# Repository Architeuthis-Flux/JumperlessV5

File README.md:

###### The next generation [jumperless](https://github.com/Architeuthis-Flux/Jumperless) breadboard
---
## If you got here by scanning the QR code on your box and want to know how to use this thing, the [There's a readthedocs.io site here](https://jumperless-docs.readthedocs.io/en/latest).
#### Don't hesitate to ask me *anything* in [Discord](https://discord.gg/Zvv7Dvgxa5) or wherever. Seriously, even if you think it's a dumb question, someone else probably has it too, so it helps me out a lot to know what to put in the guide.

Watch the launch video here:

  ---

# What is it?

Jumperless V5 lets you prototype like a nerdy wizard who can see electricity and conjure jumpers with a magic wand. It’s an Integrated Development Environment (IDE) for hardware, with an analog-by-nature RP2350B dev board, a drawer full of wires, and a workbench full of test equipment (including a power supply, a multimeter, an oscilloscope, a function generator, and a logic analyzer) all crammed inside a breadboard.

You can connect any point to any other using software-defined jumpers, so the four individually programmable ±8 V power supplies; ten GPIO; and seven management channels for voltage, current, and resistance can all be connected anywhere on the breadboard or the Arduino Nano header. RGB LEDs under each hole turn the breadboard itself into a display that provides real-time information about whatever’s happening in your circuit.

It's not just about being too lazy to plug in some jumpers. With software controlled wiring, the circuit *itself* is now [***scriptable***](08-micropython.md), which opens up a world of infinite crazy new things you could never do on a regular breadboard. Have a script try out every combination of parts until it does what you want (*à la* [evolvable hardware](https://evolvablehardware.org/)), automatically switch around audio effects on the fly, characterize some unknown chip with the part numbers sanded off, or don't bother with any of that and just [play Doom on it](https://www.youtube.com/watch?v=xWYWruUO0F4).

But more likely, you'll be using it to get circuits from your brain into hardware with so little friction it feels like you're just thinking them into existence. So yeah, wizard shit.

### **These are the docs where you will learn how to wield your new powers**

If you don't already have one,
## [Get a Jumperless V5 on Crowd Supply](https://www.crowdsupply.com/architeuthis-flux/jumperless-v5)

## Getting Started

## Documentation Sections

- **[Basic Controls](https://jumperless-docs.readthedocs.io/en/latest/01-basic-controls/)** - Learn how to use the probe, click wheel, and slot system
- **[The App](https://jumperless-docs.readthedocs.io/en/latest/03-app/)** - For talking to your Jumperless, importing from Wokwi, and flashing Arduino sketches
- **[OLED](https://jumperless-docs.readthedocs.io/en/latest/04-oled/)** - Add a better display
- **[Arduino](https://jumperless-docs.readthedocs.io/en/latest/05-arduino/)** - UART passthrough and automatic flashing
- **[Configuration](https://jumperless-docs.readthedocs.io/en/latest/06-config)** - Persistent settings
- **[Debugging](https://jumperless-docs.readthedocs.io/en/latest/07-debugging)** - Crossbar, bridge, and net list views
- **[File Manager](https://jumperless-docs.readthedocs.io/en/latest/08-file-manager)** - Filesystem access, YAML slot file editing, and text editor
- **[MicroPython](https://jumperless-docs.readthedocs.io/en/latest/08-micropython)** - Use the onboard MicroPython interpreter
- **[Odds and Ends](https://jumperless-docs.readthedocs.io/en/latest/09-odds-and-ends)** - Stuff I couldn't think of a good category for
- **[3D Printable Stand](https://jumperless-docs.readthedocs.io/en/latest/10-3d-stand)** - Print your own stand
- **[Writing Native Apps](https://jumperless-docs.readthedocs.io/en/latest/11-WritingApps)** - Dig into the actual firmware and write your own apps
- **[Glossary](https://jumperless-docs.readthedocs.io/en/latest/99-glossary)** - Key terms including slots, nodes, bridges, and the W command

---

## Find Me On The Internet

Join the [Discord](https://discord.gg/bvacV7r3FP) for pretty much instant answers to your questions

<div class="social-icons">

</div>

---

The 4 individually programmable ±8V power supplies, 5 voltage/current/resistance measurement channels, and 10 GPIO can all be connected anywhere on the breadboard or the Arduino Nano header. Connections made with its matrix of 12 analog crossbar switches can be changed in just a few microseconds, so measurements and GPIO can multiplexed to cover the entire board at once.

V5 is a major redesign of the original [Jumperless](https://github.com/Architeuthis-Flux/Jumperless). Having a few hundred people out there using Jumperlesses, sharing ideas, and [writing their](https://github.com/nilclass/jlctl) [own apps](https://github.com/nilclass/jumperlab) gave me a long enough list of things I wish I had done that I felt it was time to push the design even further. Now that the fundamentals are battle-tested (switching matrix, power supply, routing algorithm), Jumperless V5 can add some even crazier new stuff like; an ungodly number (445) of LEDs, a built in rotary encoder/switch, daisy chain headers, individually programmable power rails, and an isolated, always-on probing system. 

These additions may seem somewhat minor, but they fundamentally change the way using a Jumperless V5 *feels*. It's intuitive enough that it quickly just becomes "part of your brain" in the same way your computer does. And it's easy to forget this isn't how prototyping stuff on a breadboard always has been.

https://github.com/user-attachments/assets/c78493ee-f2cd-4704-bab7-26346f978c54

https://github.com/user-attachments/assets/168cb387-934b-4a25-b30d-b696312ee0e1

# For People Who Like Reading (btw all of this is a bit dated and some details have changed since then)
You're flipping through a comic book and see an ad in the back for some X-ray glasses. You put some coins in an envelope and send it off (because it's like 50 years ago in this made up scenario) and get back some spectacles. You immediately look up at the night sky towards the galactic center for Sagittarius A* and don't see a thing; you've been had. You go back to prototyping your new Eurorack module (because that's what I assume everyone was doing in the early 80's) and forget to take them off. 

You notice that you can now see electrons flowing, capacitors charging, frequencies changing, UART messages passing, all right there on your breadboard. Those aren't X-ray specs, they're electron specs, even better.  

###### //When the prototypes get here on Monday, I'll take proper photos and these will be replaced

*Jumperless V5 is that pair of X-ray spectacles.* Like all the fancy test equipment covering our workbenches, it converts the things that our hunter-gatherer-ass MK 1 eyeballs can't perceive into something they can. The difference is that it does it for everything, everywhere, exactly where it's happening with an RGB LED under every hole. 

Now you're prototyping in God Mode, never again will you spend 2 hours testing every possible issue just to find that your Tx and Rx lines are swapped, or you forgot to hook up the Vcc pin, or some other thing that seems absolutely obvious in retrospect but you simply didn't have the information until you went down the list and checked each thing that could possibly go wrong.

Jumper wires are another time-consuming, flow-breaking thing, so let's get rid of those too. To be able to read and write anything everywhere, it also needs to be fully jumperless, so any rows on the breadboard (and the Arduino Nano header) can be connected to any other, as well as any of the 4 programmable power supplies, 3 analog measurement channels, 2 current/resistance sensors, (supplies and measurement are all good to +-8V), or 10 GPIO (4 are 5V logic, 6 are 3.3V. All 10 can instead be routed to another daisy-chained Jumperless as fully analog connections.) 

This isn't meant to abstract away the tactile process of prototyping under a layer of software. In fact, it's just the opposite, not having your circuit hidden under a tangled mass of jumper wires gives you a breadboard that is understandable at a glance and almost reads like a schematic. You can just drop a measurement anywhere and have it displayed on the LEDs under that row so you will immediately see if anything changes in real time, so you can get a much more intuitive sense about *why* things work (or don't). It's about cutting down on the debugging bullshit and letting the grander plans for what you're building flow freely. Ideas happen at their own pace, and getting stuck on the finicky details of circuit design can break the creative momentum. 

The probe, rotary encoder, and onboard menus make connecting to a computer optional. You can do everything with only USB C power. Your past projects are saved into onboard flash as simple text files that can be uploaded to your computer and shared.

Breadboards should be a playground, and now you can attach a debug probe to them.

https://github.com/Architeuthis-Flux/JumperlessV5/assets/20519442/a3d5ecf4-4665-409d-bab6-2a62fbbe0eb7

Now you have a breadboard with:

- 4 x 12 bit DACs ([MCP4278](https://www.microchip.com/en-us/product/mcp4728)) buffered and shifted to ±8V through high current op amps ([2 L272D](https://estore.st.com/en/l272d-cpn.html))
- 3 x 12 bit ADCs (built into the RP2040) double buffered and level shifted (2 LM324) to read ±8V 
- 2 x 12 bit current/voltage sensors ([INA219](https://www.ti.com/product/INA219)) which can also be used to measure resistance
- 4 x 5V logic level GPIO ([MCP23S17](https://www.microchip.com/en-us/product/mcp23s17))
- 6 x 3.3V logic level GPIO ([RP2040](https://www.raspberrypi.com/documentation/microcontrollers/rp2040.html)) which can also be hardware I2C, UART, or SPI
- 1 x ±8V op amp noninverting buffer ([LM324](https://www.ti.com/product/LM324B))
- 2 x 14 pin daisy chain headers on either side to pass 8 analog signals + SPI + Power to another Jumperless
- A probe to select rows without affecting connections (TRRRS jack with I2C)
- A rotary encoder / switch ([SIQ-02FVS3](https://www.lcsc.com/product-detail/Rotary-Encoders_Mitsumi-Electric-SIQ-02FVS3_C2925423.html))
- 445 addressable RGB LEDs ([XL-1010RGBC](https://www.lcsc.com/product-detail/Light-Emitting-Diodes-LED_XINGLIGHT-XL-1010RGBC-WS2812B_C5349953.html))

You can see how all this stuff is connected in the [schematic](https://kicanvas.org/?github=https://github.com/Architeuthis-Flux/JumperlessV5/blob/main/Hardware/JumperlessV5hw/JumperlessV5hw.kicad_sch).

Or check out the [PCB](https://kicanvas.org/?github=https://github.com/Architeuthis-Flux/JumperlessV5/blob/main/Hardware/JumperlessV5hw/JumperlessV5hw.kicad_pcb) and [GitHub repo](https://github.com/Architeuthis-Flux/JumperlessV5)

All these things are routable to anywhere on the breadboard or Nano header in a few microseconds under the control of the onboard RP2040. This freedom to script connections and measurements and route outputs anywhere presumably makes just about any random circuit on the Jumperless V5 Turing complete. There are an infinite number of things you could make this thing do, and the Prime Directive is to make those awesome hacks as simple and straightforward to pull off as possible. 

But for now, I'll only talk about things I've written firmware for that is currently supported without any hacking required.

Jumperless V5 accepts commands and stores connections in a ridiculously simple, human readable format that you can just drop onto the board as a text file. You can save a bunch of these net lists into persistent storage and switch between them at your whim. It will even accept connections from whatever's plugged into the Nano header (or anywhere else on the board over UART).

```
f {ADC1-10, 15-48, TOP_RAIL-17, TOP_RAIL>6.5V, D0-UART_Rx, D1-UART_Tx, }
```
⬆︎ *that's it, that's everything you need to send it to make things happen*

You can see how all that firmware works in the [firmware section of the GitHub repo]([https://github.com/Architeuthis-Flux/JumperlessV5](https://github.com/Architeuthis-Flux/JumperlessV5/tree/main/JumperlessV5firmware))

## The Probe
Jumperless V5 uses a string of 92 ±0.1% precision resistors in a huge voltage divider and one of the ADC channels to sense which number the probe is poking. The probe itself is very simple, just a button, an LED, and a pokey needle to touch the sensing pads. It connects to the main board with a TRRRS 1/8" audio jack. It also has I2C and power available on there for future hacking purposes (in case someone wants to stick an OLED on the probe, the code already does send signals for an SSD1306 display). 

If you happen to misplace your probe, the way it's designed allows you to just plug in any random 1/8" audio cable and poke out connections with the tip.

###### Just pretend this has an audio cable stuck to the back and it's sitting on a V5

## The App
The desktop app allows you to assign up to 8 [Wokwi](https://wokwi.com/) projects to separate slots that are polled for changes and automatically updated on the Jumperless V5 (within half a second of clicking Save). Or if you don't want to use Wokwi, it simply acts as a regular terminal emulator like PuTTY, xTerm, Serial, etc. You could also just use any of those, the menus are sent and handled on the Jumperless itself, the Jumperless desktop app just adds automatic firmware updates, Wokwi polling, and arduino-cli for flashing code from your Wokwi sketch to the Arduino via a single USB cable.

## Serial/I2C/SPI/MIDI
Jumperless V5 can sniff or write any UART, I2C, SPI, or MIDI signals on the board. It can be set to either print whatever it reads on the breadboard LEDs, turning the Jumperless into a serial monitor and/or show up as 2 USB devices to your computer and give you bidirectional communication through that other port. 
Look at that, Jumperless just saved you $3 on one of those little USB-UART boards, it practically pays for itself!!1!

## Slots/Music
The firmware saves multiple netlists in separate text files. You can save/load/manage the various slots through a serial terminal, the onboard menus, or even crazier things like having the slot change based on a Eurorack CV (control voltage) signal or whatever. So Jumperless can be incorporated into your modular synth setup as a way to switch between a bunch of patches live on the fly. The switchover time from one setup to another is quick enough to be inaudible.

## Voltage/Current Limits
The CMOS analog switches inside these CH446Qs can only block or pass voltages that are between their power supply rails. They're powered with an [LT1054CP](https://www.ti.com/product/LT1054) charge pump voltage doubler/inverter circuit that produces ~±9V. So it can handle any voltages between +9V and -9V and ~100mA per connection.
You may notice that these values are well outside the absolute maximum ratings (14.6V and 10mA per connection) listed in the CH446Q datasheet. That's because they are, all the specifications of the CH446Q get better as the supply voltage increases, so I'm exploiting the arcane weirdness of CMOS to get closer to an ideal switch. All of this is unchanged from the original Jumperless, so it's been well tested. 

## On resistance
Okay, here's the main bummer here. As it turns out, we live in a universe governed by both physics and capitalism, so manufacturers only make chips they think people will buy. The [CH446Q](https://www.wch-ic.com/products/CH446.html) (and the [MT8816](https://www.microsemi.com/product-directory/analog-cross-point-switches/4920-mt8816) it was based on) were made with radio, video, and audio in mind, which is much more concerned with frequency response than acting like an idealized jumper wire that can pass a bunch of current. So the total resistance for a jumperless connection is ~90Ω (45Ω for each pass through an overdriven crosspoint switch). For most circuits, this really doesn't have a noticeable effect. The beauty of the Jumperless V5 is that it can show you when that resistance is affecting your circuit and tell you to place an old-school jumper wire on that connection like it's the 1800s.

###### If this campaign does well enough, the next project will be making a general purpose crossbar switch out of beefy MOSFETs and [floating gate](https://en.wikipedia.org/wiki/Floating-gate_MOSFET) drivers to get the voltage limits into the ±50V range and the R<sub>on</sub> down to ~1Ω, but custom high-current silicon is a huge, expensive undertaking (that I am 100% committed to doing)

## Frequency Response
The [CH446Q](https://www.wch-ic.com/products/CH446.html) analog crosspoint switches used here have a 3dB rolloff (1/2 the signal amplitude is passed, not a hard limit) of 50MHz, which is well above any breadboard's rolloff frequency (the clip-plastic-clip between each row is effectively a tiny capacitor.) So even for super high speed SPI signals, this really isn't an issue. Modern (last ~30 years) input buffers on ICs are just amazing. TL;DR In regards to frequency, if it works on a regular breadboard, it will work on this.

## Repairability
If you're worried about messing up one of the a spring clips and ruining your Jumperless, fear not! The breadboard shell is removable, so you can easily remove the shell and replace the offending clip (5-6 spares will be included). 

This is really just for peace of mind. These clips are made of spring-tempered phosphor bronze, which is what they use for super high quality breadboards, and they're pretty hard to permanently bend out of shape. 

The other cool bonus of having removable shells is that you can print your own in any color/material you like and swap it out. The stock shell is 3D printed in black SLS PA-12 Nylon.

When you buy a Jumperless, you're also buying the right so have a *working* Jumperless forever. There's literally nothing you can do to break it so badly that I won't happily fix or replace it for free. If you want to fix it yourself, I will send you any parts you need and walk you through the repair. 

## Open Sourciness
This thing is infinitely open source and hackable. I'm kind of a zealot about that stuff. Want to make 10 of these with a USB Mini port for you and your friends? Let me know and I'll double check everything when you're putting in the PCB order to make sure all the parts are placed correctly and stuff (and I'd totally buy one, I love USB Mini). I'll even send you the custom spring clips.

If you have some feature you want to add, I'm happy to help. Either by just adding it myself or walking you through the relevant bits of code to make it happen.

https://github.com/user-attachments/assets/703db848-5871-4152-bb03-244a400a1bb8

https://github.com/user-attachments/assets/f4ce75e4-14b6-48c8-96ba-9c4a3180d78c

https://github.com/user-attachments/assets/7bf4f20c-272e-4586-8e50-9da7c20dedf6

https://github.com/user-attachments/assets/13d6d9ab-8ea0-4387-aee6-343be06bf343

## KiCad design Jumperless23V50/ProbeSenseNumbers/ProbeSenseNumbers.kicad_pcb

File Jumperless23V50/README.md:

# Jumperless V5
 The next generation [jumperless breadboard](https://github.com/Architeuthis-Flux/Jumperless)

More LEDs, fewer jumpers!

Here in this folder there *should* be every bit of hardware that goes into this thing. If something's missing, just ask.

Anyway here's a render of each of the parts you'll find in these folders:

Here's a list of the new stuff being added to V5:
- a separate probe sensing system  (so rows can be selected without disconnecting and scanning the whole board)
- 5 LEDs under each row  (so the breadboard itself can display measurements, text, video, whatever)
- a rotary encoder/button  (so you can navigate menus without looking at a computer)
- 10 GPIO (4 5V, 6 3.3V) that can be routed anywhere  (so you can talk to chips on the breadboard, or logic analyze them)
- a daisy chain header on both sides  (so you can stick a bunch of these together and route 8 fully analog signals between boards)
- a TRRRS audio jack for the probe  (so you can select rows, measure voltage and add an I2C display)
- 2 arbitrarily programmable power rails  (so you can set each one separately to any voltage within +-8V)
- 2 more routable high-current DACs, 3 +- 8V buffered ADCs, a routable op amp buffer (so you're not losing any features of the original Jumperless)
- a USB-C port  (so you can shut the fuck up about my love for USB Mini)

https://github.com/Architeuthis-Flux/JumperlessV5/assets/20519442/e1003ef1-e145-4110-8218-d5403845bdf6

https://github.com/Architeuthis-Flux/JumperlessV5/assets/20519442/8845355e-0e21-4cbd-b4f0-f0b5bd2063a3

https://github.com/Architeuthis-Flux/JumperlessV5/assets/20519442/c6f371e6-8d97-4a70-bf3b-5532be4f0662

https://github.com/Architeuthis-Flux/JumperlessV5/assets/20519442/ceb898b4-bbbe-4788-ab80-29add00364f6

https://github.com/Architeuthis-Flux/JumperlessV5/assets/20519442/f67fb13e-432d-4cfa-b7df-fb754a4e1074

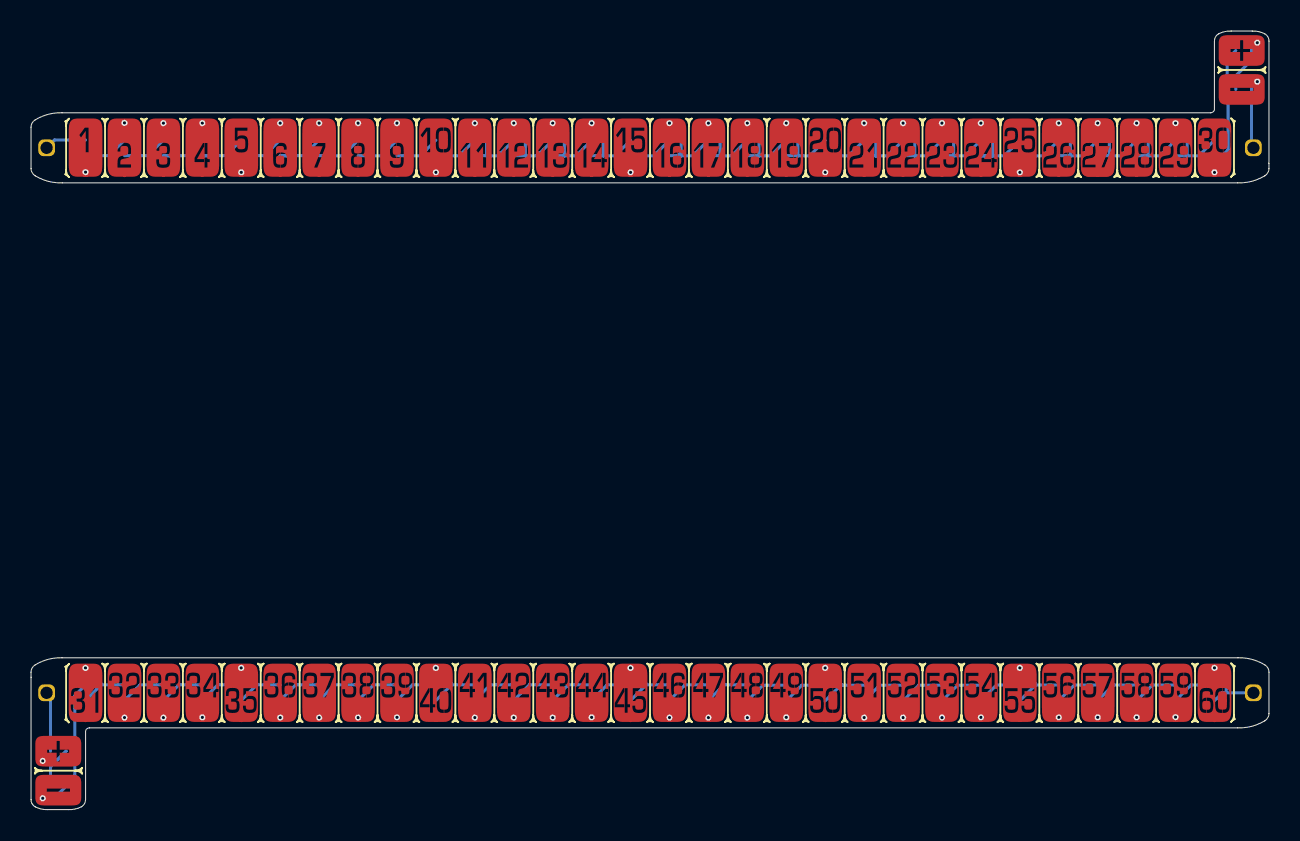
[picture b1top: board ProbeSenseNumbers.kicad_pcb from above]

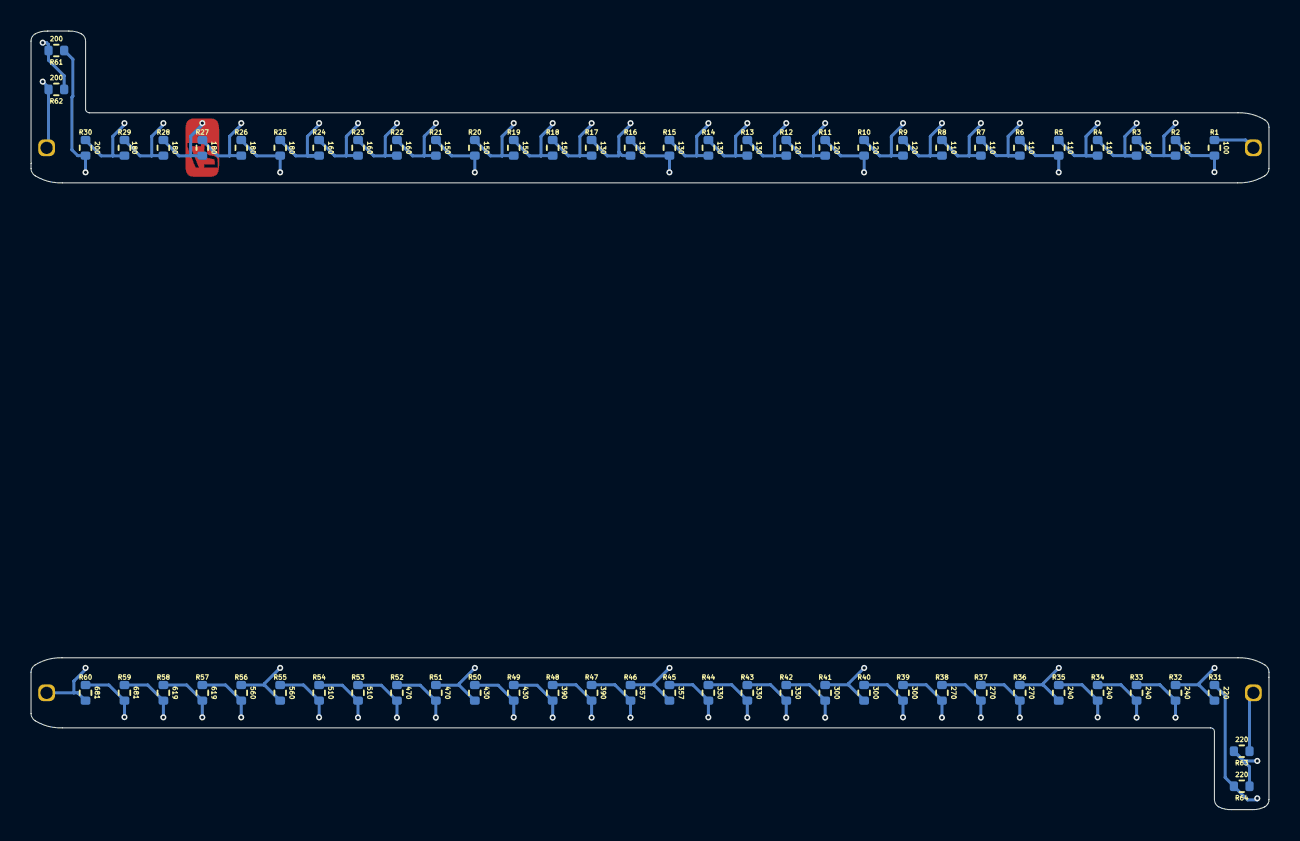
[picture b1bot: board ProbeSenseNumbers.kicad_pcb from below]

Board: 2 copper layers, 80.8 x 50.8 mm, 72 parts (64 on the bottom side), 66 nets.

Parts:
J3: TopIn; PinHeader_1x1_Smallest
J4: BottomOut; PinHeader_1x1_Smallest
J31: + - top; bbProbeContactsRails
J32: + - bottom; bbProbeContactsRails
J34: TopOut; PinHeader_1x1_Smallest
J35: BottomIn; PinHeader_1x1_Smallest
R1, R2, R3: 100; R_0402_1005Metric
R4, R5, R6, R7, R8: 110; R_0402_1005Metric
R9, R10, R11, R12: 120; R_0402_1005Metric
R13, R14, R15, R16, R17: 130; R_0402_1005Metric
R18, R19, R20, R21: 150; R_0402_1005Metric
R22, R23, R24: 160; R_0402_1005Metric
R25, R26, R27, R28, R29: 180; R_0402_1005Metric
R30, R61, R62: 200; R_0402_1005Metric
R31, R63, R64: 220; R_0402_1005Metric
R32, R33, R34, R35: 240; R_0402_1005Metric
R36, R37, R38: 270; R_0402_1005Metric
R39, R40, R41: 300; R_0402_1005Metric
R42, R43, R44: 330; R_0402_1005Metric
R45, R46: 357; R_0402_1005Metric
R47, R48: 390; R_0402_1005Metric
R49, R50: 430; R_0402_1005Metric
R51, R52: 470; R_0402_1005Metric
R53, R54: 510; R_0402_1005Metric
R55, R56: 560; R_0402_1005Metric
R57, R58: 619; R_0402_1005Metric
R59, R60: 681; R_0402_1005Metric
U1: bbProbeContactsTopRow
U3: bbProbeContactsBottomRow

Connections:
unnamed: J3.1, R1.1
unnamed: J4.1, R60.2, U3.60
unnamed: J31.1, R61.2, R62.1
unnamed: J31.2, J34.1, R62.2
unnamed: J32.1, R63.2, R64.1
unnamed: J32.2, R31.1, R64.2
unnamed: J35.1, R63.1
unnamed: R1.2, R2.1, U1.1
unnamed: R2.2, R3.1, U1.2
unnamed: R3.2, R4.1, U1.3
unnamed: R4.2, R5.1, U1.4
unnamed: R5.2, R6.1, U1.5
unnamed: R6.2, R7.1, U1.6
unnamed: R7.2, R8.1, U1.7
unnamed: R8.2, R9.1, U1.8
unnamed: R9.2, R10.1, U1.9
unnamed: R10.2, R11.1, U1.10
unnamed: R11.2, R12.1, U1.11
unnamed: R12.2, R13.1, U1.12
unnamed: R13.2, R14.1, U1.13
unnamed: R14.2, R15.1, U1.14
unnamed: R15.2, R16.1, U1.15
unnamed: R16.2, R17.1, U1.16
unnamed: R17.2, R18.1, U1.17
unnamed: R18.2, R19.1, U1.18
unnamed: R19.2, R20.1, U1.19
unnamed: R20.2, R21.1, U1.20
unnamed: R21.2, R22.1, U1.21
unnamed: R22.2, R23.1, U1.22
unnamed: R23.2, R24.1, U1.23
unnamed: R24.2, R25.1, U1.24
unnamed: R25.2, R26.1, U1.25
unnamed: R26.2, R27.1, U1.26
unnamed: R27.2, R28.1, U1.27
unnamed: R28.2, R29.1, U1.28
unnamed: R29.2, R30.1, U1.29
unnamed: R30.2, R61.1, U1.30
unnamed: R31.2, R32.1, U3.31
unnamed: R32.2, R33.1, U3.32
unnamed: R33.2, R34.1, U3.33
unnamed: R34.2, R35.1, U3.34
unnamed: R35.2, R36.1, U3.35
unnamed: R36.2, R37.1, U3.36
unnamed: R37.2, R38.1, U3.37
unnamed: R38.2, R39.1, U3.38
unnamed: R39.2, R40.1, U3.39
unnamed: R40.2, R41.1, U3.40
unnamed: R41.2, R42.1, U3.41
unnamed: R42.2, R43.1, U3.42
unnamed: R43.2, R44.1, U3.43
unnamed: R44.2, R45.1, U3.44
unnamed: R45.2, R46.1, U3.45
unnamed: R46.2, R47.1, U3.46
unnamed: R47.2, R48.1, U3.47
unnamed: R48.2, R49.1, U3.48
unnamed: R49.2, R50.1, U3.49
unnamed: R50.2, R51.1, U3.50
unnamed: R51.2, R52.1, U3.51
unnamed: R52.2, R53.1, U3.52
unnamed: R53.2, R54.1, U3.53
unnamed: R54.2, R55.1, U3.54
unnamed: R55.2, R56.1, U3.55
unnamed: R56.2, R57.1, U3.56
unnamed: R57.2, R58.1, U3.57
unnamed: R58.2, R59.1, U3.58
unnamed: R59.2, R60.1, U3.59

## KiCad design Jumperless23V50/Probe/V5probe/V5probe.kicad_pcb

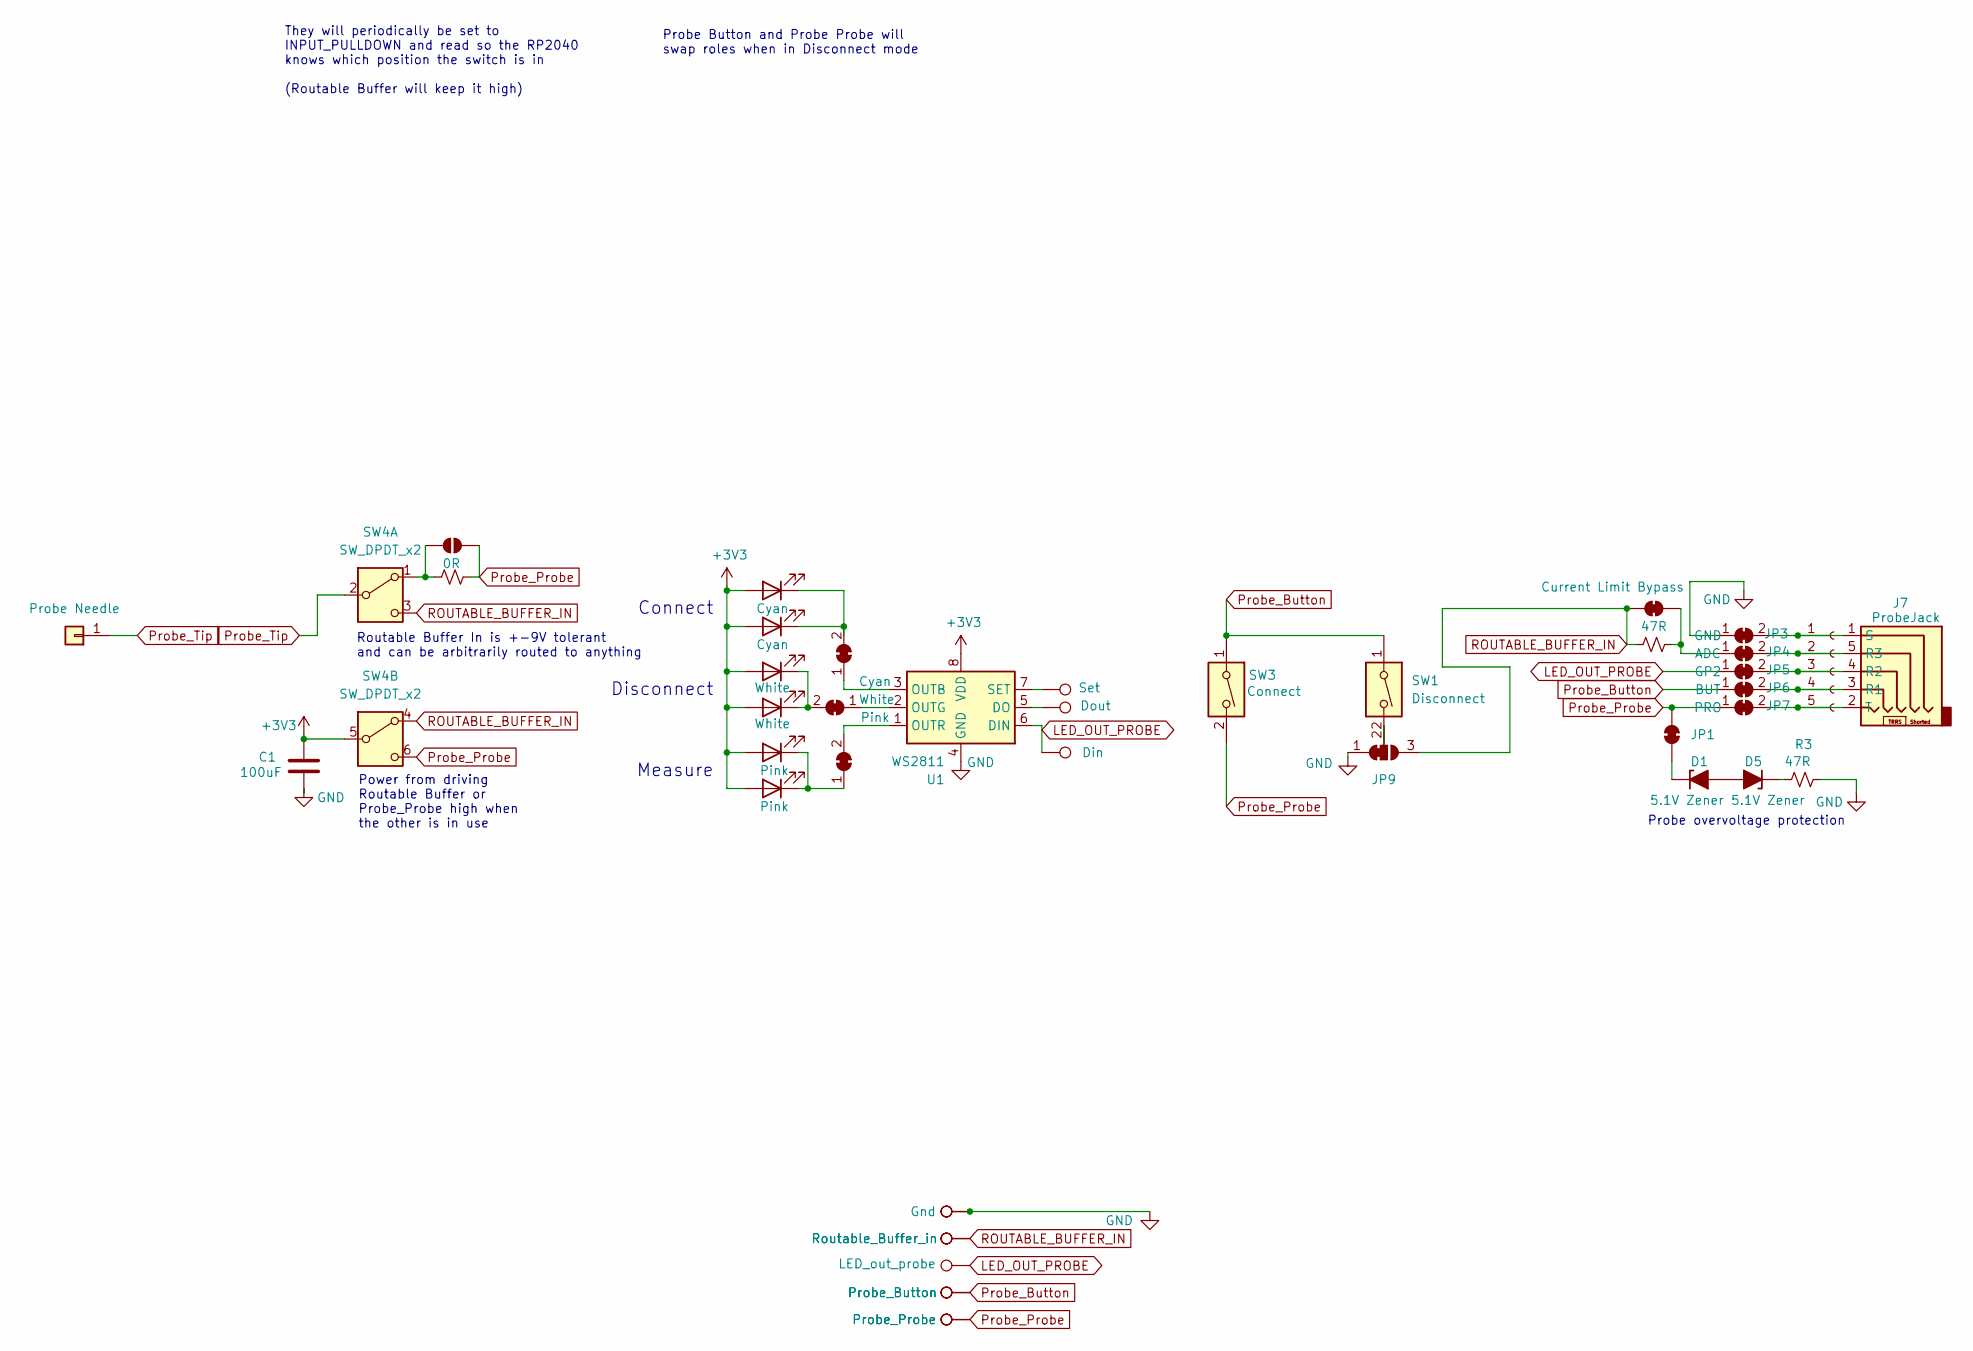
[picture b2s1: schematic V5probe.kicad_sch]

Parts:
C1: 100uF; C_1206_3216Metric_Pad1.33x1.80mm_HandSolder
D1, D5: 5.1V Zener; D_SOD-323_HandSoldering; LCSC C18547704
D2, D6: Pink; LED_4014; LCSC C7371931
D3, D8: Cyan; LED_4014; LCSC C7371929
D4, D7: White; LED_4014; LCSC C3646959
J1: Conn_01x05_Socket
J2: Probe Needle; ProbeNeedle
J7: ProbeJack; STX_3452_TRRRS_Audio_Jack
JP1, JP2: SolderJumper_2_Bridged; SolderJumper_2_Bridged_Small
JP3: GND; SolderJumper_2_Bridged_Small
JP4: ADC; SolderJumper_2_Bridged_Small
JP5: GP2; SolderJumper_2_Bridged_Small
JP6: BUT; SolderJumper_2_Bridged_Small
JP7: PRO; SolderJumper_2_Bridged_Small
JP8: Current Limit Bypass; SolderJumper_2_Bridged_Small
JP9: SolderJumper_3_Bridged12; SolderJumper-3_P1.3mm_Bridged12_Pad1.0x1.5mm
R1: 0R; R_0603_1608Metric_Pad0.98x0.95mm_HandSolder
R2, R3: 47R; R_0603_1608Metric_Pad0.98x0.95mm_HandSolder; LCSC Part # C2907043
SW1: Disconnect; TS6634_Tact_Switch; LCSC C557614
SW3: Connect; TS6634_Tact_Switch; LCSC C557614
SW4: SW_DPDT_x2; XKB_SK3245S-L3-A_DPDT_Slide_Switch; LCSC C405952
TP1: Dout; TestPoint_D0.75mm
TP2: Set; TestPoint_D0.75mm
TP3: Din; TestPoint_D0.75mm
TP4, TP10: Gnd; TestPoint_D0.75mm
TP5, TP11: Routable_Buffer_in; TestPoint_D0.75mm
TP6: LED_out_probe; TestPoint_D0.75mm
TP7, TP12: Probe_Button; TestPoint_D0.75mm
TP8, TP13: Probe_Probe; TestPoint_D0.75mm
TP14: Pink; SolderJumper_2_Bridged_Small
TP15: White; SolderJumper_2_Bridged_Small
TP16: Cyan; SolderJumper_2_Bridged_Small
U1: WS2811; SOP-8_3.9x4.9mm_P1.27mm; LCSC C114581

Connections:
+3V3: C1.1, D2.2 (A), D3.2 (A), D4.2 (A), D6.2 (A), D7.2 (A), D8.2 (A), SW4.5 (B), U1.8 (VDD); also elsewhere on the board
GND: C1.2, JP3.1 (A), JP9.1 (A), R3.1, TP4.1, TP10.1, U1.4 (GND); also elsewhere on the board
LED_OUT_PROBE: JP5.1 (A), TP3.1, TP6.1, U1.6 (DIN); also elsewhere on the board
unnamed: D1.2 (A), D5.2 (A)
unnamed: D1.1 (K), JP1.1 (A)
unnamed: D2.1 (K), D6.1 (K), TP14.1 (A)
unnamed: D3.1 (K), D8.1 (K), TP16.2 (B)
unnamed: D4.1 (K), D7.1 (K), TP15.2 (B)
unnamed: D5.1 (K), R3.2
unnamed: J1.1, J7.1 (S), JP3.2 (B)
unnamed: J1.2, J7.5 (R3), JP4.2 (B)
unnamed: J1.3, J7.4 (R2), JP5.2 (B)
unnamed: J1.4, J7.3 (R1), JP6.2 (B)
unnamed: J1.5, J7.2 (T), JP7.2 (B)
unnamed: JP2.1 (A), R1.1, SW4.1 (A)
unnamed: JP4.1 (A), JP8.2 (B), R2.2
unnamed: JP9.2 (C), SW1.2
unnamed: TP14.2 (B), U1.1 (OUTR)
unnamed: TP15.1 (A), U1.2 (OUTG)
unnamed: TP16.1 (A), U1.3 (OUTB)
unnamed: TP1.1, U1.5 (DO)
unnamed: TP2.1, U1.7 (SET)
Probe_Button: JP6.1 (A), SW1.1, SW3.1, TP7.1, TP12.1; also elsewhere on the board
Probe_Probe: JP1.2 (B), JP2.2 (B), JP7.1 (A), R1.2, SW3.2, SW4.6 (C), TP8.1, TP13.1; also elsewhere on the board
Probe_Tip: J2.1, SW4.2 (B)
ROUTABLE_BUFFER_IN: JP8.1 (A), JP9.3 (B), R2.1, SW4.3 (C), SW4.4 (A), TP5.1, TP11.1; also elsewhere on the board

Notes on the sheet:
Probe Button and Probe Probe will swap roles when in Disconnect mode
They will periodically be set to INPUT_PULLDOWN and read so the RP2040 knows which position the switch is in (Routable Buffer will keep it high)
Power from driving Routable Buffer or Probe_Probe high when the other is in use
Routable Buffer In is +-9V tolerant and can be arbitrarily routed to anything
Probe overvoltage protection
Connect Disconnect Measure

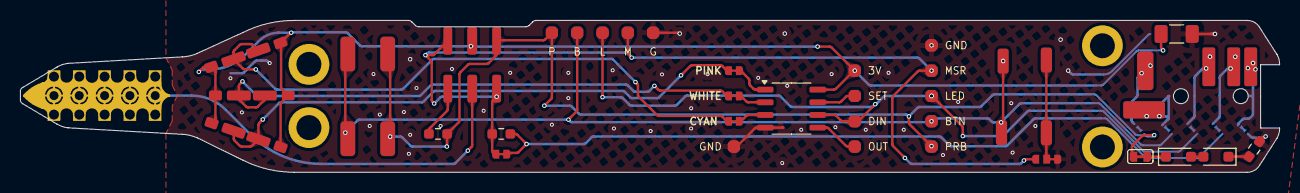
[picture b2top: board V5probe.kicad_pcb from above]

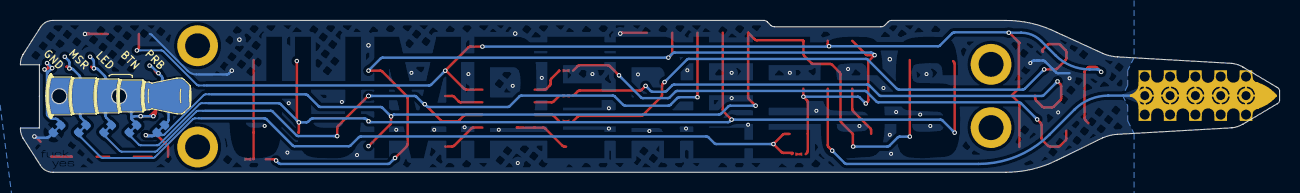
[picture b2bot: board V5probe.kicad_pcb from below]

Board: 2 copper layers, 126.4 x 15.2 mm, 49 parts (7 on the bottom side), 26 nets.

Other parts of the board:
P1, P2, P3, P4: M1.6_SMT_Screw_Post 3mm Height; M1.6_SMT_Screw_Post
TP3#2, TP9: Din; TestPoint_D0.75mm
TP4#2: Gnd; TestPoint_D0.75mm
TP5#2: Routable_Buffer_in; TestPoint_D0.75mm
TP7#2: Probe_Button; TestPoint_D0.75mm
TP8#2: Probe_Probe; TestPoint_D0.75mm

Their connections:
+3V3: TP9.1; also elsewhere on the board
GND: TP4#2.1; also elsewhere on the board
LED_OUT_PROBE: TP3#2.1; also elsewhere on the board
Probe_Button: TP7#2.1; also elsewhere on the board
Probe_Probe: TP8#2.1; also elsewhere on the board
ROUTABLE_BUFFER_IN: TP5#2.1; also elsewhere on the board

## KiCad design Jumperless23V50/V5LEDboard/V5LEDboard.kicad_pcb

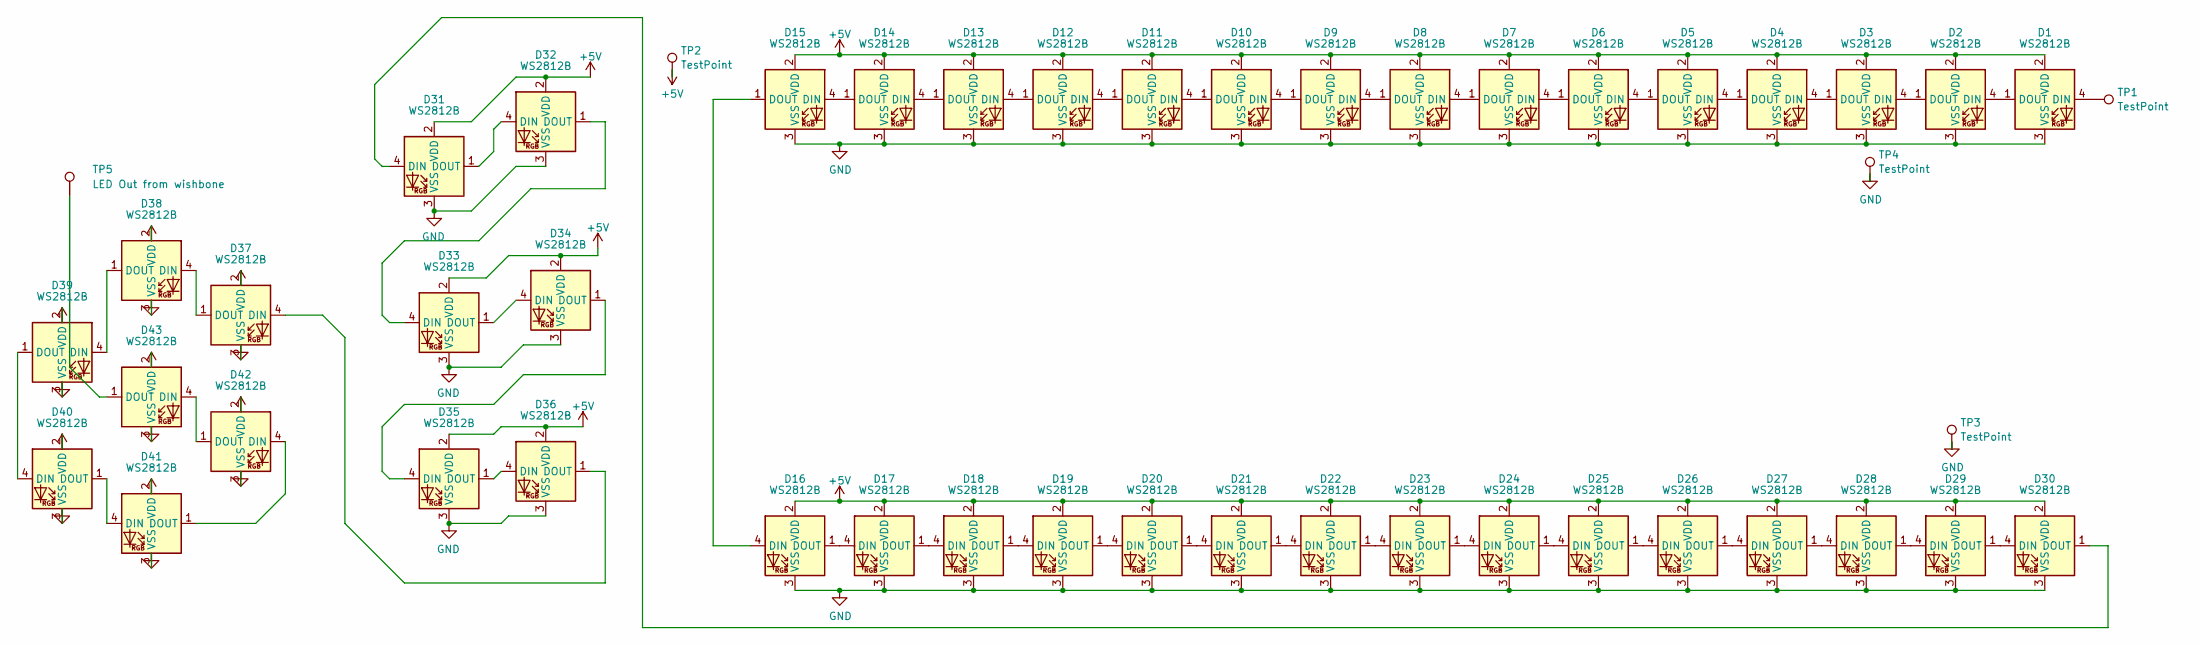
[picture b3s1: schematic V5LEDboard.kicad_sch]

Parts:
D1, D2, D3, D4, D5, D6, D7, D8, D9, D10, D11, D12, D13, D14, D15, D16, D17, D18, D19, D20, D21, D22, D23, D24, D25, D26, D27, D28, D29, D30, D31, D32, D33, D34, D35, D36, D37, D38, D39, D40, D41, D42, D43: WS2812B; XL-1010RGBC-WS2812B
TP1, TP2, TP3, TP4: TestPoint; PINHEADER-1x1_vertical
TP5: LED Out from wishbone; PINHEADER-1x1_vertical

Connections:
+5V: D1.2 (VDD), D2.2 (VDD), D3.2 (VDD), D4.2 (VDD), D5.2 (VDD), D6.2 (VDD), D7.2 (VDD), D8.2 (VDD), D9.2 (VDD), D10.2 (VDD), D11.2 (VDD), D12.2 (VDD), D13.2 (VDD), D14.2 (VDD), D15.2 (VDD), D16.2 (VDD), D17.2 (VDD), D18.2 (VDD), D19.2 (VDD), D20.2 (VDD), D21.2 (VDD), D22.2 (VDD), D23.2 (VDD), D24.2 (VDD), D25.2 (VDD), D26.2 (VDD), D27.2 (VDD), D28.2 (VDD), D29.2 (VDD), D30.2 (VDD), D31.2 (VDD), D32.2 (VDD), D33.2 (VDD), D34.2 (VDD), D35.2 (VDD), D36.2 (VDD), D37.2 (VDD), D38.2 (VDD), D39.2 (VDD), D40.2 (VDD), D41.2 (VDD), D42.2 (VDD), D43.2 (VDD), TP2.1
GND: D1.3 (VSS), D2.3 (VSS), D3.3 (VSS), D4.3 (VSS), D5.3 (VSS), D6.3 (VSS), D7.3 (VSS), D8.3 (VSS), D9.3 (VSS), D10.3 (VSS), D11.3 (VSS), D12.3 (VSS), D13.3 (VSS), D14.3 (VSS), D15.3 (VSS), D16.3 (VSS), D17.3 (VSS), D18.3 (VSS), D19.3 (VSS), D20.3 (VSS), D21.3 (VSS), D22.3 (VSS), D23.3 (VSS), D24.3 (VSS), D25.3 (VSS), D26.3 (VSS), D27.3 (VSS), D28.3 (VSS), D29.3 (VSS), D30.3 (VSS), D31.3 (VSS), D32.3 (VSS), D33.3 (VSS), D34.3 (VSS), D35.3 (VSS), D36.3 (VSS), D37.3 (VSS), D38.3 (VSS), D39.3 (VSS), D40.3 (VSS), D41.3 (VSS), D42.3 (VSS), D43.3 (VSS), TP3.1, TP4.1
unnamed: D1.4 (DIN), TP1.1
unnamed: D1.1 (DOUT), D2.4 (DIN)
unnamed: D2.1 (DOUT), D3.4 (DIN)
unnamed: D3.1 (DOUT), D4.4 (DIN)
unnamed: D4.1 (DOUT), D5.4 (DIN)
unnamed: D5.1 (DOUT), D6.4 (DIN)
unnamed: D6.1 (DOUT), D7.4 (DIN)
unnamed: D7.1 (DOUT), D8.4 (DIN)
unnamed: D8.1 (DOUT), D9.4 (DIN)
unnamed: D9.1 (DOUT), D10.4 (DIN)
unnamed: D10.1 (DOUT), D11.4 (DIN)
unnamed: D11.1 (DOUT), D12.4 (DIN)
unnamed: D12.1 (DOUT), D13.4 (DIN)
unnamed: D13.1 (DOUT), D14.4 (DIN)
unnamed: D14.1 (DOUT), D15.4 (DIN)
unnamed: D15.1 (DOUT), D16.4 (DIN)
unnamed: D16.1 (DOUT), D17.4 (DIN)
unnamed: D17.1 (DOUT), D18.4 (DIN)
unnamed: D18.1 (DOUT), D19.4 (DIN)
unnamed: D19.1 (DOUT), D20.4 (DIN)
unnamed: D20.1 (DOUT), D21.4 (DIN)
unnamed: D21.1 (DOUT), D22.4 (DIN)
unnamed: D22.1 (DOUT), D23.4 (DIN)
unnamed: D23.1 (DOUT), D24.4 (DIN)
unnamed: D24.1 (DOUT), D25.4 (DIN)
unnamed: D25.1 (DOUT), D26.4 (DIN)
unnamed: D26.1 (DOUT), D27.4 (DIN)
unnamed: D27.1 (DOUT), D28.4 (DIN)
unnamed: D28.1 (DOUT), D29.4 (DIN)
unnamed: D29.1 (DOUT), D30.4 (DIN)
unnamed: D30.1 (DOUT), D31.4 (DIN)
unnamed: D31.1 (DOUT), D32.4 (DIN)
unnamed: D32.1 (DOUT), D33.4 (DIN)
unnamed: D33.1 (DOUT), D34.4 (DIN)
unnamed: D34.1 (DOUT), D35.4 (DIN)
unnamed: D35.1 (DOUT), D36.4 (DIN)
unnamed: D36.1 (DOUT), D37.4 (DIN)
unnamed: D37.1 (DOUT), D38.4 (DIN)
unnamed: D38.1 (DOUT), D39.4 (DIN)
unnamed: D39.1 (DOUT), D40.4 (DIN)
unnamed: D40.1 (DOUT), D41.4 (DIN)
unnamed: D41.1 (DOUT), D42.4 (DIN)
unnamed: D42.1 (DOUT), D43.4 (DIN)
unnamed: D43.1 (DOUT), TP5.1

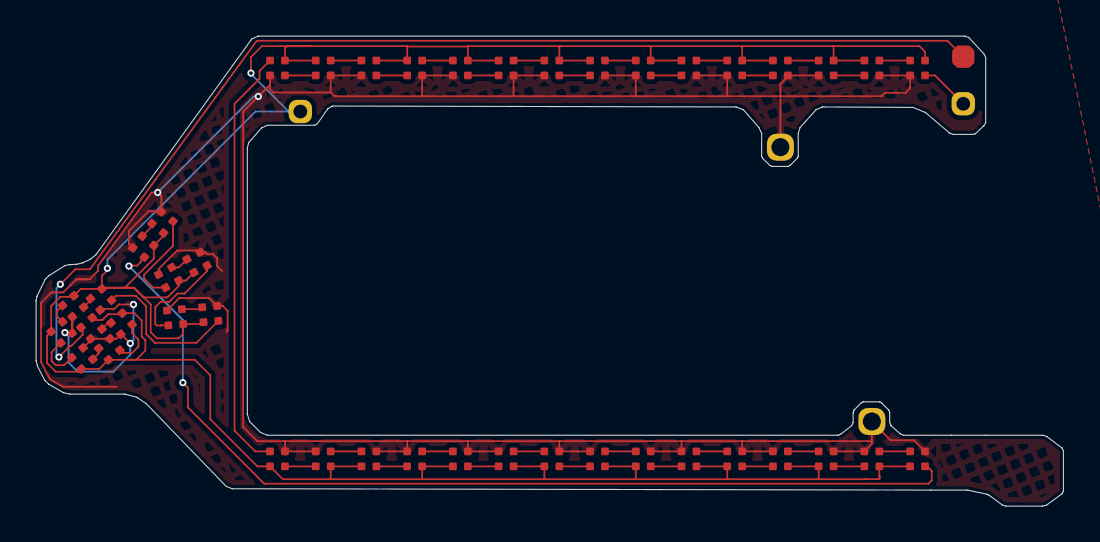
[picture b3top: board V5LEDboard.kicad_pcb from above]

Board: 2 copper layers, 57.1 x 26.1 mm, 48 parts (0 on the bottom side), 46 nets.

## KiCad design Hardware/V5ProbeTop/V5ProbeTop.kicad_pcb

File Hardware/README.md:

# Jumperless V5
 The next generation [jumperless breadboard](https://github.com/Architeuthis-Flux/Jumperless)

More LEDs, fewer jumpers!

Here in this folder there *should* be every bit of hardware that goes into this thing. If something's missing, just ask.

Anywate here's a render of each of the parts you'll find in these folders:

Here's a list of the new stuff being added to V5:
- a separate probe sensing system  (so rows can be selected without disconnecting and scanning the whole board)
- 5 LEDs under each row  (so the breadboard itself can display measurements, text, video, whatever)
- a rotary encoder/button  (so you can navigate menus without looking at a computer)
- 10 GPIO (4 5V, 6 3.3V) that can be routed anywhere  (so you can talk to chips on the breadboard, or logic analyze them)
- a daisy chain header on both sides  (so you can stick a bunch of these together and route 8 fully analog signals between boards)
- a TRRRS audio jack for the probe  (so you can select rows, measure voltage and add an I2C display)
- 2 arbitrarily programmable power rails  (so you can set each one separately to any voltage within +-8V)
- 2 more routable high-current DACs, 3 +- 8V buffered ADCs, a routable op amp buffer (so you're not losing any features of the original Jumperless)
- a USB-C port  (so you can shut the fuck up about my love for USB Mini)

https://github.com/Architeuthis-Flux/JumperlessV5/assets/20519442/e1003ef1-e145-4110-8218-d5403845bdf6

https://github.com/Architeuthis-Flux/JumperlessV5/assets/20519442/8845355e-0e21-4cbd-b4f0-f0b5bd2063a3

https://github.com/Architeuthis-Flux/JumperlessV5/assets/20519442/c6f371e6-8d97-4a70-bf3b-5532be4f0662

https://github.com/Architeuthis-Flux/JumperlessV5/assets/20519442/ceb898b4-bbbe-4788-ab80-29add00364f6

https://github.com/Architeuthis-Flux/JumperlessV5/assets/20519442/f67fb13e-432d-4cfa-b7df-fb754a4e1074

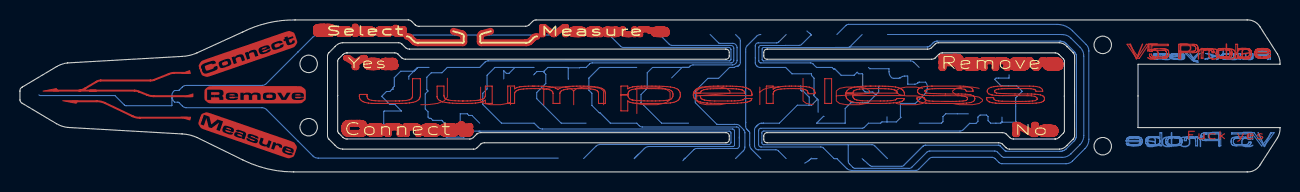
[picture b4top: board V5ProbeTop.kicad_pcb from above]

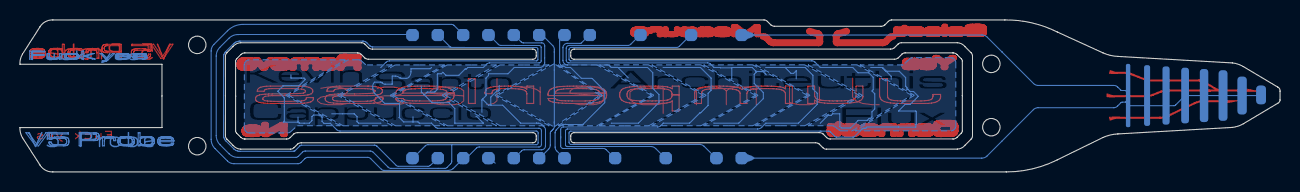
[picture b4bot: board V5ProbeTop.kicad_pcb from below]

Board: 2 copper layers, 126.4 x 15.2 mm, 30 parts (30 on the bottom side), 14 nets.

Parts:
J1, J2: Conn_01x13_Socket; Probe_capsense_connect
TP1, TP2, TP3, TP4, TP5, TP6, TP7, TP8, TP9, TP10, TP11, TP12, TP13, TP14, TP15, TP16, TP17, TP18, TP19, TP20, TP21, TP22, TP23, TP24, TP25, TP26, TP27, TP28: TestPoint; Tiniest_Possible_pad

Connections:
unnamed: J1.1, J2.1, TP14.1, TP28.1
unnamed: J1.2, J2.2, TP13.1, TP27.1
unnamed: J1.3, J2.3, TP12.1, TP26.1
unnamed: J1.4, J2.4, TP11.1, TP25.1
unnamed: J1.5, J2.5, TP10.1, TP24.1
unnamed: J1.6, J2.6, TP9.1, TP23.1
unnamed: J1.7, J2.7, TP8.1, TP22.1
unnamed: J1.8, J2.8, TP7.1, TP21.1
unnamed: J2.9, TP6.1, TP20.1
unnamed: J1.10, TP5.1, TP19.1
unnamed: J2.11, TP4.1, TP18.1
unnamed: J1.12, TP3.1, TP17.1
unnamed: J2.13, TP2.1, TP16.1
unnamed: J1.14, TP1.1, TP15.1
